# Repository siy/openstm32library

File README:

This repository is aimed to contain various libraries for OpenSTM32 project 
(see https://github.com/gbulmer/openstm32sw and https://github.com/gbulmer/openstm32hw)

General approach to repository layout:

Top level subdirectories:

\- human-interface                     <- Everything related to LCD/OLED/TFT/LED displays, keyboards, etc.
\- networking-communication-navigation <- Ethernet, Wi-Fi, GSM, GPS, BT, ZigBee, RF, etc.
\- sensors-conversion                  <- Everything related to sensors (temperature, humidity, acceleration, etc.) and DAC/ADC.
\- control                             <- All things related to power control/lighting/motors/etc.)
\- algorithms                          <- Useful general purpose code, statistics, signal processing, control algorithms (such as PID), etc.

Suggested library layout:

\- <top level directory>
   \- <chip/module/board/algorithm name>
     \- wirish       <- class, header and other stuff necessary to enable use of library in Maple IDE (optional for non-wiring libraries)
     \- examples     <- optional examples for library
     \- hardware     <- optional hardware designs (breakout boards, etc.)
     \- src          <- library sources (optional, but suggested for general purpose algorithms and non-wiring libraries)
     README          <- library README

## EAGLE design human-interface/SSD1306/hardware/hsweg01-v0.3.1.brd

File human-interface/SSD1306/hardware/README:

Simple breakout board for the UG-2864HSWEG01 display. Since STM32F1/2/4 series are 3.3V devices,
no additional voltage level shifting is required. Note that no connectors/adapters for display
are required, display is designed for direct soldering to PCB.

The design is Copyright (C) 2011-2012 Sergiy Yevtushenko and is covered by
CC BY-SA license version 3.0 (http://creativecommons.org/licenses/by-sa/3.0/).

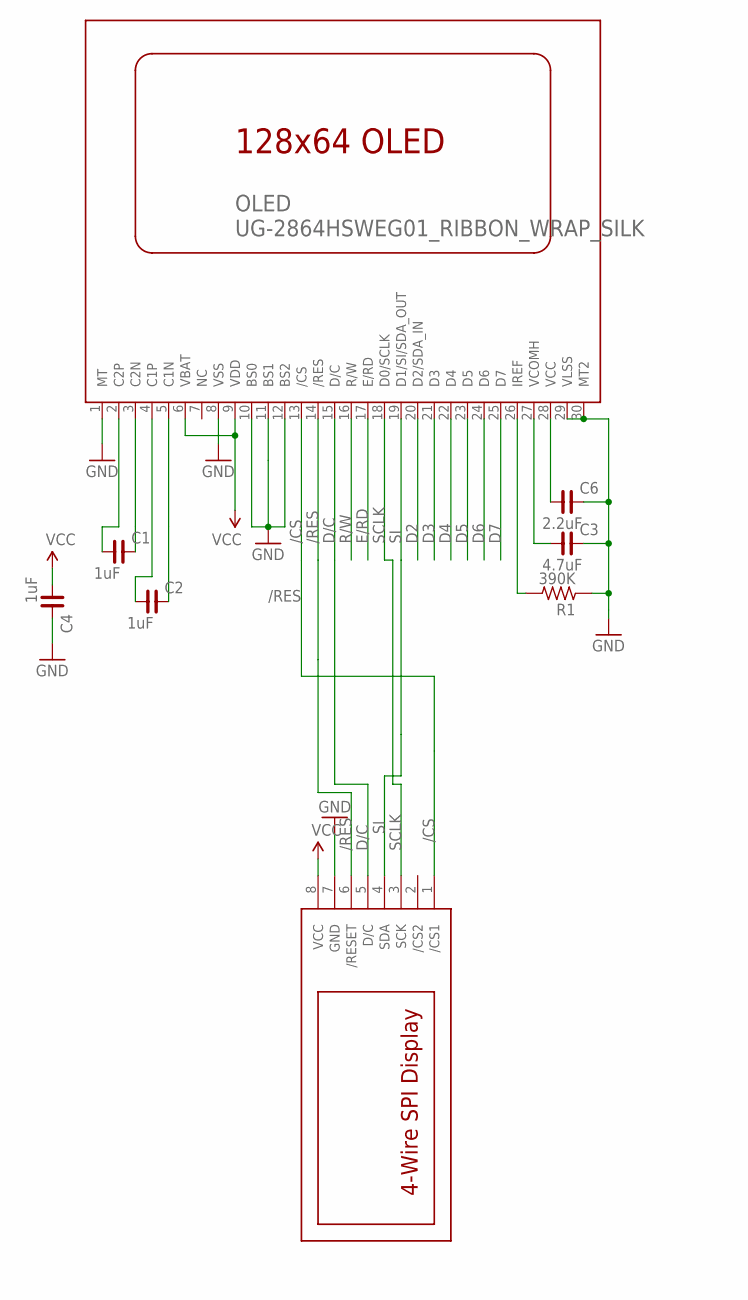
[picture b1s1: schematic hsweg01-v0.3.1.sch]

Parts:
C1, C2, C4: 1uF; C0603
C3: 4.7uF; C0805
C6: 2.2uF; C0805
OLED: UG-2864HSWEG01_RIBBON_WRAP_SILK; UG-2864HSWEG01
R1: 390K; R0603
U$1: 4W-SPI-DISP; 1X08-NOSILK

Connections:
/CS: OLED.13 (/CS), U$1.1 (/CS1)
/RES: OLED.14 (/RES), U$1.6 (/RESET)
D2: OLED.20 (D2/SDA_IN)
D3: OLED.21 (D3)
D4: OLED.22 (D4)
D5: OLED.23 (D5)
D6: OLED.24 (D6)
D7: OLED.25 (D7)
D/C: OLED.15 (D/C), U$1.5 (D/C)
E/RD: OLED.17 (E/RD)
GND: C3.2, C4.2, C6.2, OLED.1 (MT), OLED.8 (VSS), OLED.10 (BS0), OLED.11 (BS1), OLED.12 (BS2), OLED.29 (VLSS), OLED.30 (MT2), R1.1, U$1.7 (GND)
unnamed: C6.1, OLED.28 (VCC)
unnamed: C1.2, OLED.3 (C2N)
unnamed: C1.1, OLED.2 (C2P)
unnamed: C2.1, OLED.4 (C1P)
unnamed: C2.2, OLED.5 (C1N)
unnamed: OLED.26 (IREF), R1.2
unnamed: C3.1, OLED.27 (VCOMH)
R/W: OLED.16 (R/W)
SCLK: OLED.18 (D0/SCLK), U$1.3 (SCK)
SI: OLED.19 (D1/SI/SDA_OUT), U$1.4 (SDA)
VCC: C4.1, OLED.6 (VBAT), OLED.9 (VDD), U$1.8 (VCC)

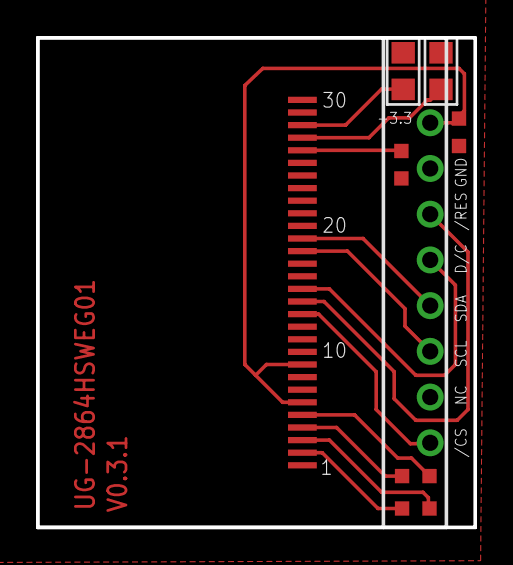
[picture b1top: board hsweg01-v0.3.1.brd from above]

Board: 2 copper layers, 24.3 x 27.2 mm, 8 parts (0 on the bottom side), 14 nets.

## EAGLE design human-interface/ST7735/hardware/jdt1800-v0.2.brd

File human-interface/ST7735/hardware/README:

Simple breakout board for the JDT-1800 TFT LCD display.
Note that no connectors/adapters for display are required, display 
is designed for direct soldering to PCB.

The design is Copyright (C) 2011-2012 Sergiy Yevtushenko and is covered by
CC BY-SA license version 3.0 (http://creativecommons.org/licenses/by-sa/3.0/).

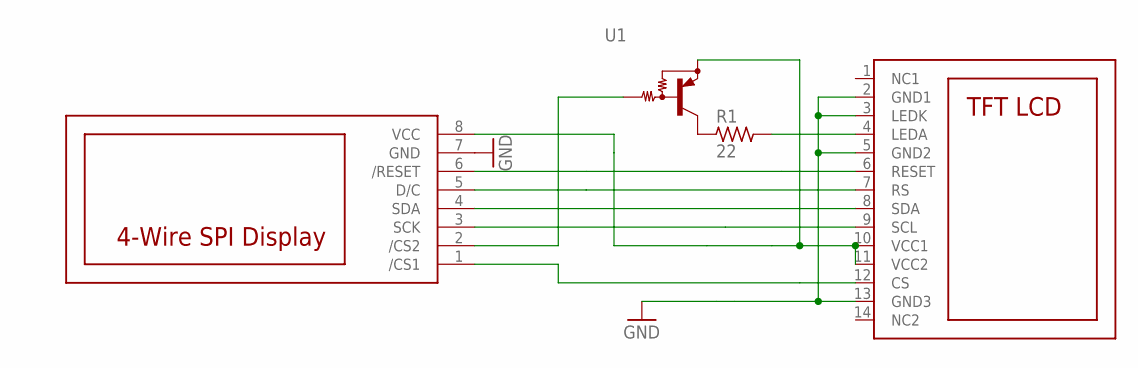
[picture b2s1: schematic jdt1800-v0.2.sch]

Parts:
R1: 22; R0603
U1: PNP-DRIVERSOT323; SOT323R
U$1: TFT1.8"; 1.8TFT
U$2: 4W-SPI-DISP; 1X08-NOSILK

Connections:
GND: U$1.2 (GND1), U$1.3 (LEDK), U$1.5 (GND2), U$1.13 (GND3), U$2.7 (GND)
unnamed: R1.1, U1.3 (C)
unnamed: U1.2 (E), U$1.10 (VCC1), U$1.11 (VCC2), U$2.8 (VCC)
unnamed: U1.1 (B), U$2.2 (/CS2)
unnamed: U$1.6 (RESET), U$2.6 (/RESET)
unnamed: U$1.7 (RS), U$2.5 (D/C)
unnamed: U$1.8 (SDA), U$2.4 (SDA)
unnamed: U$1.9 (SCL), U$2.3 (SCK)
unnamed: U$1.12 (CS), U$2.1 (/CS1)
unnamed: R1.2, U$1.4 (LEDA)

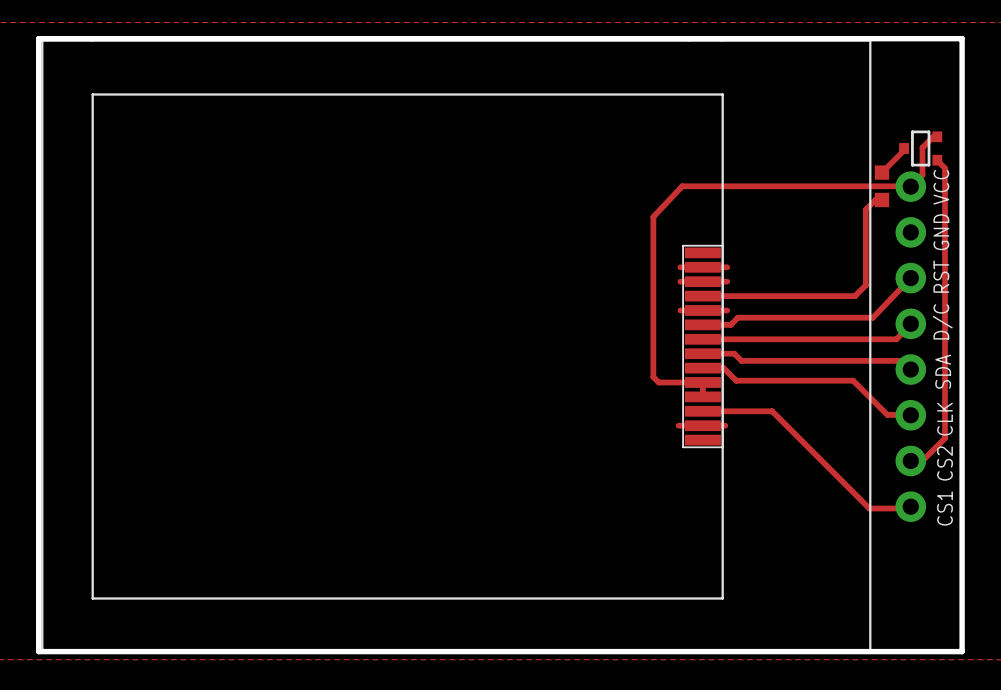
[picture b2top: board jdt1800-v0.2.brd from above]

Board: 2 copper layers, 51.3 x 34.1 mm, 4 parts (0 on the bottom side), 10 nets.

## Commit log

2012-04-15 Added libraries for SSD1306 and ST7735
